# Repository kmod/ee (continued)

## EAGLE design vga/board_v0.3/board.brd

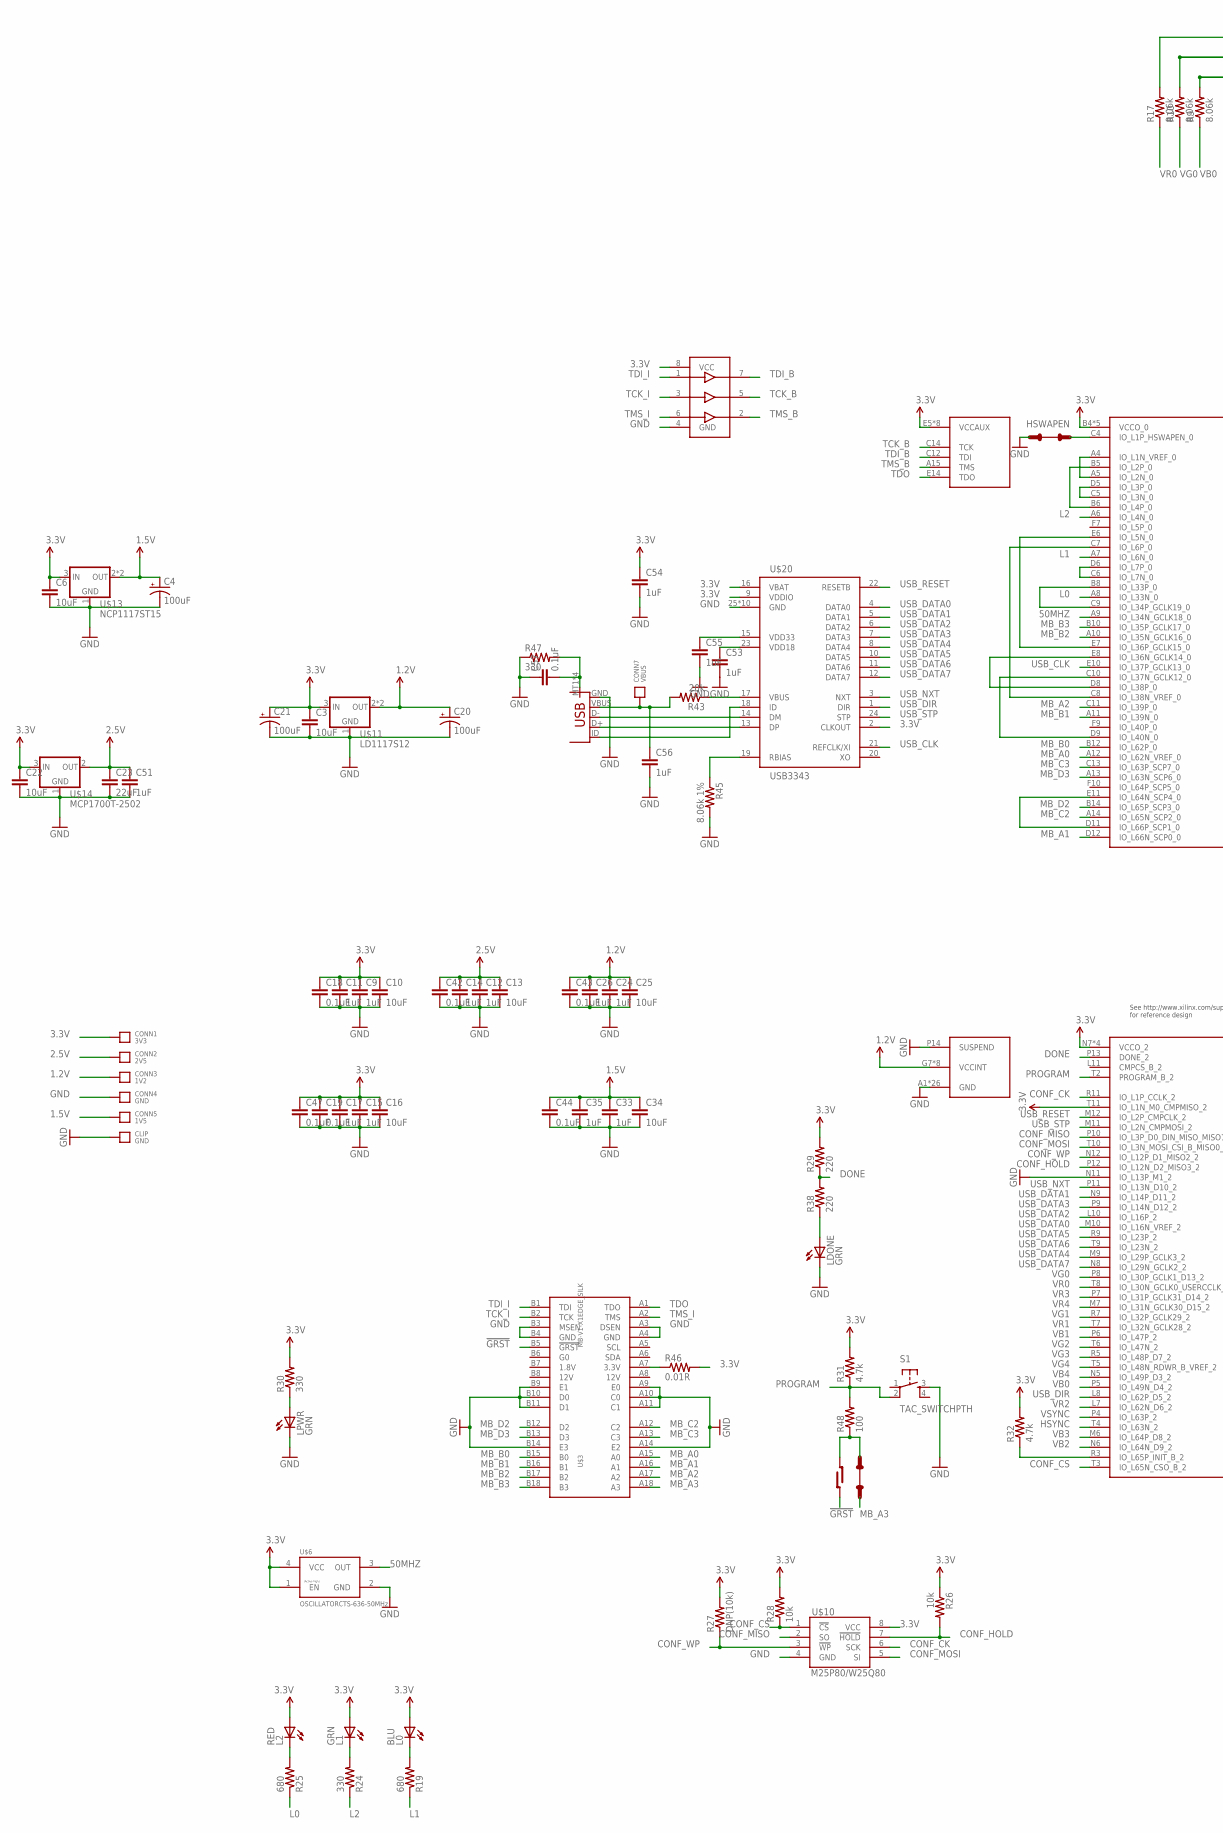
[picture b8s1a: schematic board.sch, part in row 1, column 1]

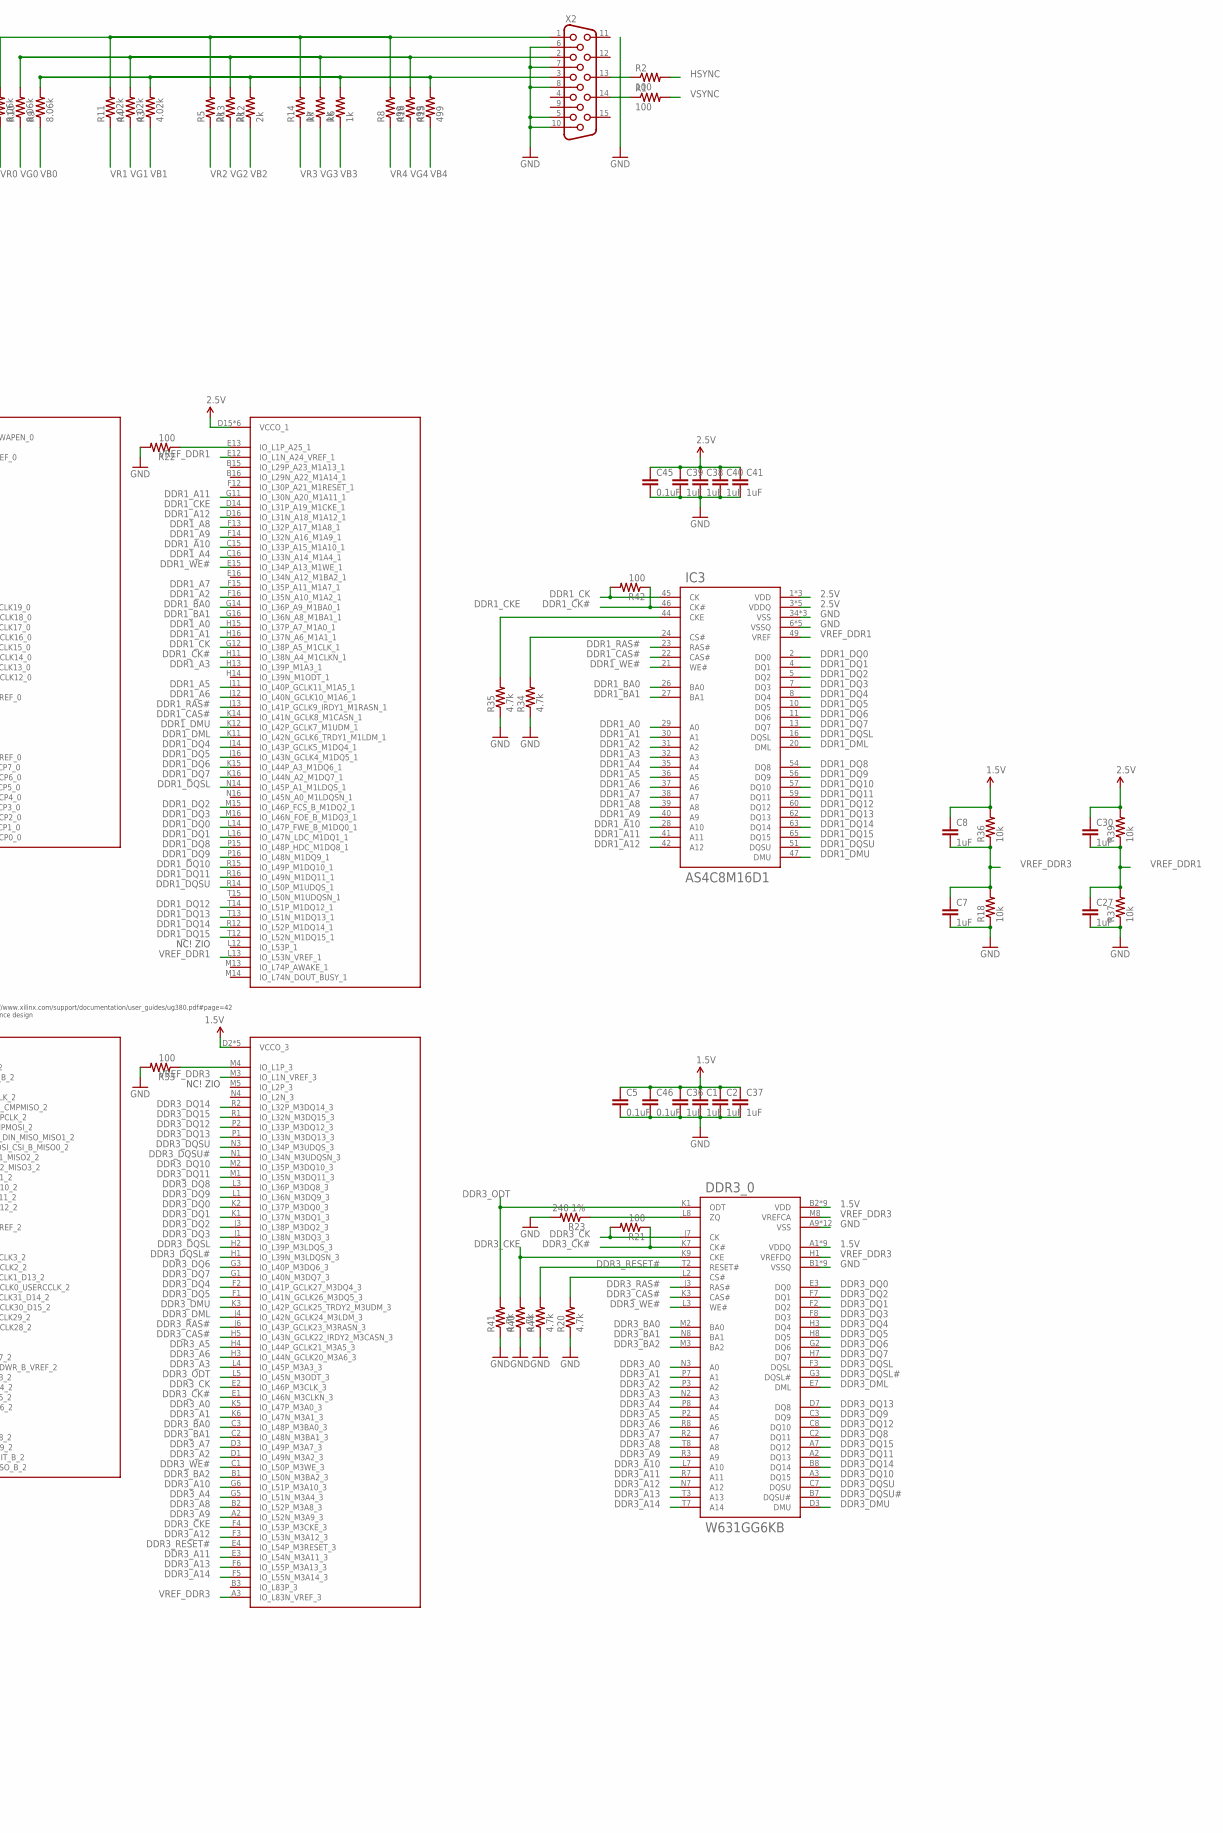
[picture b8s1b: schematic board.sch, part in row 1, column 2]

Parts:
C1, C2, C7, C8, C9, C11, C12, C14, C15, C17, C24, C26, C27, C30, C33, C35, C36, C37, C38, C39, C40, C41, C51, C53, C54, C55, C56: 1uF; 0402-CAP
C3, C6, C10, C13, C16, C22, C25, C34: 10uF; 0603-CAP
C4, C20, C21: 100uF; CAP-5-2
C5, C18, C19, C42, C43, C44, C45, C46, C47: 0.1uF; C0201
C23: 22uF; 0805
C57: 0.1uF; 0402-CAP
CLIP: GND; CLIP-AREA
CONN1: 3V3; HOLE_22AWG
CONN2: 2V5; HOLE_22AWG
CONN3: 1V2; HOLE_22AWG
CONN4: GND; HOLE_22AWG
CONN5: 1V5; HOLE_22AWG
CONN7: VBUS; HOLE_22AWG
DDR3_0: W631GG6KB; BGA96
IC1: XC6S{9,16,25}LX-FT256; XILINX_FT256
IC2: 74LVC3G34; TSSOP8
IC3: AS4C8M16D1; TSOP66-400
JP1: USBMICRO; USB-MICRO
L0: BLU; 0603_LED
L1: GRN; 0603_LED
L2: RED; 0603_LED
LDONE: GRN; 0603_LED
LPWR: GRN; 0603_LED
R1, R2, R21, R22, R33, R48: 100; 0603-RES
R3, R4, R11: 4.02k; 0603-RES
R5, R12, R13: 2k; 0603-RES
R6, R7, R14: 1k; 0603-RES
R8, R15, R16: 499; 0603-RES
R9, R10, R17: 8.06k; 0603-RES
R18, R28, R36, R37, R39: 10k; 0603-RES
R19, R25: 680; 0603-RES
R20, R34, R35, R40, R41, R44: 4.7k; 0402-RES
R23: 240 1%; 0402-RES
R24, R30, R47: 330; 0603-RES
R26: 10k; 0402-RES
R27: DNP(10k); 0402-RES
R29, R38: 220; 0603-RES
R31, R32: 4.7k; 0603-RES
R42: 100; 0402-RES
R43: 20k; 0402-RES
R45: 8.06k 1%; 0603-RES
R46: 0.01R; 0603-RES
S1: TAC_SWITCHPTH; TACTILE-PTH
SB1: SOLDER-BRIDGEOPEN; SOLDER-BRIDGE-OPEN
SB2, SB5: TRACE-CUT
U$3: MB-V1-X1EDGE_SILK; MB-V1-X1-EDGE
U$6: OSCILLATORCTS-636-50MHz; CTS-636
U$10: M25P80/W25Q80; SO08
U$11: LD1117S12; SOT223
U$13: NCP1117ST15; SOT223
U$14: MCP1700T-2502; SOT23-3
U$20: USB3343; QFN24
X2: HDF15H

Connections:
1.2V: C20.1 (+), C24.1, C25.1, C26.1, C43.1, CONN3.P, IC1.G7 (VCCINT), IC1.G9 (VCCINT), IC1.H8 (VCCINT), IC1.H10 (VCCINT), IC1.J7 (VCCINT), IC1.J9 (VCCINT), IC1.K8 (VCCINT), IC1.K10 (VCCINT), U$11.2 (OUT), U$11.4 (OUT)
1.5V: C1.1, C2.1, C4.1 (+), C5.1, C8.1, C33.1, C34.1, C35.1, C36.1, C37.1, C44.1, C46.1, CONN5.P, DDR3_0.A1 (VDDQ), DDR3_0.A8 (VDDQ), DDR3_0.B2 (VDD), DDR3_0.C1 (VDDQ), DDR3_0.C9 (VDDQ), DDR3_0.D2 (VDDQ), DDR3_0.D9 (VDD), DDR3_0.E9 (VDDQ), DDR3_0.F1 (VDDQ), DDR3_0.G7 (VDD), DDR3_0.H2 (VDDQ), DDR3_0.H9 (VDDQ), DDR3_0.K2 (VDD), DDR3_0.K8 (VDD), DDR3_0.N1 (VDD), DDR3_0.N9 (VDD), DDR3_0.R1 (VDD), DDR3_0.R9 (VDD), IC1.D2 (VCCO_3), IC1.G4 (VCCO_3), IC1.J2 (VCCO_3), IC1.K4 (VCCO_3), IC1.N2 (VCCO_3), R36.2, U$13.2 (OUT), U$13.4 (OUT)
2.5V: C12.1, C13.1, C14.1, C23.1, C30.1, C38.1, C39.1, C40.1, C41.1, C42.1, C45.1, C51.1, CONN2.P, IC1.D15 (VCCO_1), IC1.G13 (VCCO_1), IC1.J15 (VCCO_1), IC1.K13 (VCCO_1), IC1.N15 (VCCO_1), IC1.R13 (VCCO_1), IC3.1 (VDD), IC3.3 (VDDQ), IC3.9 (VDDQ), IC3.15 (VDDQ), IC3.18 (VDD), IC3.33 (VDD), IC3.55 (VDDQ), IC3.61 (VDDQ), R39.2, U$14.2 (OUT)
3.3V: C3.1, C6.1, C9.1, C10.1, C11.1, C15.1, C16.1, C17.1, C18.1, C19.1, C21.1 (+), C22.1, C47.1, C54.1, CONN1.P, IC1.B4 (VCCO_0), IC1.B9 (VCCO_0), IC1.B13 (VCCO_0), IC1.D7 (VCCO_0), IC1.D10 (VCCO_0), IC1.E5 (VCCAUX), IC1.F8 (VCCAUX), IC1.F11 (VCCAUX), IC1.G10 (VCCAUX), IC1.H6 (VCCAUX), IC1.J10 (VCCAUX), IC1.L6 (VCCAUX), IC1.L9 (VCCAUX), IC1.N7 (VCCO_2), IC1.N10 (VCCO_2), IC1.R4 (VCCO_2), IC1.R8 (VCCO_2), IC1.T11 (IO_L1N_M0_CMPMISO_2), IC2.8 (VCC), L0.A, L1.A, L2.A, R26.1, R27.2, R28.2, R29.2, R30.2, R31.2, R32.2, R46.2, U$6.1 (EN), U$6.4 (VCC), U$10.8 (VCC), U$11.3 (IN), U$13.3 (IN), U$14.3 (IN), U$20.2 (CLKOUT), U$20.9 (VDDIO), U$20.16 (VBAT)
50MHZ: IC1.A9 (IO_L34N_GCLK18_0), U$6.3 (OUT)
!GRST: SB1.L1, SB1.L2, U$3.B5 (!GRST)
CONF_CK: IC1.R11 (IO_L1P_CCLK_2), U$10.6 (SCK)
CONF_CS: IC1.T3 (IO_L65N_CSO_B_2), R28.1, U$10.1 (!CS)
CONF_HOLD: IC1.P12 (IO_L12N_D2_MISO3_2), R26.2, U$10.7 (!HOLD)
CONF_MISO: IC1.P10 (IO_L3P_D0_DIN_MISO_MISO1_2), U$10.2 (SO)
CONF_MOSI: IC1.T10 (IO_L3N_MOSI_CSI_B_MISO0_2), U$10.5 (SI)
CONF_WP: IC1.N12 (IO_L12P_D1_MISO2_2), R27.1, U$10.3 (!WP)
DDR1_A0: IC1.H15 (IO_L37P_A7_M1A0_1), IC3.29 (A0)
DDR1_A1: IC1.H16 (IO_L37N_A6_M1A1_1), IC3.30 (A1)
DDR1_A2: IC1.F16 (IO_L35N_A10_M1A2_1), IC3.31 (A2)
DDR1_A3: IC1.H13 (IO_L39P_M1A3_1), IC3.32 (A3)
DDR1_A4: IC1.C16 (IO_L33N_A14_M1A4_1), IC3.35 (A4)
DDR1_A5: IC1.J11 (IO_L40P_GCLK11_M1A5_1), IC3.36 (A5)
DDR1_A6: IC1.J12 (IO_L40N_GCLK10_M1A6_1), IC3.37 (A6)
DDR1_A7: IC1.F15 (IO_L35P_A11_M1A7_1), IC3.38 (A7)
DDR1_A8: IC1.F13 (IO_L32P_A17_M1A8_1), IC3.39 (A8)
DDR1_A9: IC1.F14 (IO_L32N_A16_M1A9_1), IC3.40 (A9)
DDR1_A10: IC1.C15 (IO_L33P_A15_M1A10_1), IC3.28 (A10)
DDR1_A11: IC1.G11 (IO_L30N_A20_M1A11_1), IC3.41 (A11)
DDR1_A12: IC1.D16 (IO_L31N_A18_M1A12_1), IC3.42 (A12)
DDR1_BA0: IC1.G14 (IO_L36P_A9_M1BA0_1), IC3.26 (BA0)
DDR1_BA1: IC1.G16 (IO_L36N_A8_M1BA1_1), IC3.27 (BA1)
DDR1_CAS#: IC1.K14 (IO_L41N_GCLK8_M1CASN_1), IC3.22 (CAS#)
DDR1_CK: IC1.G12 (IO_L38P_A5_M1CLK_1), IC3.45 (CK), R42.2
DDR1_CK#: IC1.H11 (IO_L38N_A4_M1CLKN_1), IC3.46 (CK#), R42.1
DDR1_CKE: IC1.D14 (IO_L31P_A19_M1CKE_1), IC3.44 (CKE), R35.2
DDR1_CS#: IC3.24 (CS#), R34.2
DDR1_DML: IC1.K11 (IO_L42N_GCLK6_TRDY1_M1LDM_1), IC3.20 (DML)
DDR1_DMU: IC1.K12 (IO_L42P_GCLK7_M1UDM_1), IC3.47 (DMU)
DDR1_DQ0: IC1.L14 (IO_L47P_FWE_B_M1DQ0_1), IC3.2 (DQ0)
DDR1_DQ1: IC1.L16 (IO_L47N_LDC_M1DQ1_1), IC3.4 (DQ1)
DDR1_DQ2: IC1.M15 (IO_L46P_FCS_B_M1DQ2_1), IC3.5 (DQ2)
DDR1_DQ3: IC1.M16 (IO_L46N_FOE_B_M1DQ3_1), IC3.7 (DQ3)
DDR1_DQ4: IC1.J14 (IO_L43P_GCLK5_M1DQ4_1), IC3.8 (DQ4)
DDR1_DQ5: IC1.J16 (IO_L43N_GCLK4_M1DQ5_1), IC3.10 (DQ5)
DDR1_DQ6: IC1.K15 (IO_L44P_A3_M1DQ6_1), IC3.11 (DQ6)
DDR1_DQ7: IC1.K16 (IO_L44N_A2_M1DQ7_1), IC3.13 (DQ7)
DDR1_DQ8: IC1.P15 (IO_L48P_HDC_M1DQ8_1), IC3.54 (DQ8)
DDR1_DQ9: IC1.P16 (IO_L48N_M1DQ9_1), IC3.56 (DQ9)
DDR1_DQ10: IC1.R15 (IO_L49P_M1DQ10_1), IC3.57 (DQ10)
DDR1_DQ11: IC1.R16 (IO_L49N_M1DQ11_1), IC3.59 (DQ11)
DDR1_DQ12: IC1.T14 (IO_L51P_M1DQ12_1), IC3.60 (DQ12)
DDR1_DQ13: IC1.T13 (IO_L51N_M1DQ13_1), IC3.62 (DQ13)
DDR1_DQ14: IC1.R12 (IO_L52P_M1DQ14_1), IC3.63 (DQ14)
DDR1_DQ15: IC1.T12 (IO_L52N_M1DQ15_1), IC3.65 (DQ15)
DDR1_DQSL: IC1.N14 (IO_L45P_A1_M1LDQS_1), IC3.16 (DQSL)
DDR1_DQSU: IC1.R14 (IO_L50P_M1UDQS_1), IC3.51 (DQSU)
DDR1_RAS#: IC1.J13 (IO_L41P_GCLK9_IRDY1_M1RASN_1), IC3.23 (RAS#)
DDR1_WE#: IC1.E15 (IO_L34P_A13_M1WE_1), IC3.21 (WE#)
DDR3_A0: DDR3_0.N3 (A0), IC1.K5 (IO_L47P_M3A0_3)
DDR3_A1: DDR3_0.P7 (A1), IC1.K6 (IO_L47N_M3A1_3)
DDR3_A2: DDR3_0.P3 (A2), IC1.D1 (IO_L49N_M3A2_3)
DDR3_A3: DDR3_0.N2 (A3), IC1.L4 (IO_L45P_M3A3_3)
DDR3_A4: DDR3_0.P8 (A4), IC1.G5 (IO_L51N_M3A4_3)
DDR3_A5: DDR3_0.P2 (A5), IC1.H4 (IO_L44P_GCLK21_M3A5_3)
DDR3_A6: DDR3_0.R8 (A6), IC1.H3 (IO_L44N_GCLK20_M3A6_3)
DDR3_A7: DDR3_0.R2 (A7), IC1.D3 (IO_L49P_M3A7_3)
DDR3_A8: DDR3_0.T8 (A8), IC1.B2 (IO_L52P_M3A8_3)
DDR3_A9: DDR3_0.R3 (A9), IC1.A2 (IO_L52N_M3A9_3)
DDR3_A10: DDR3_0.L7 (A10), IC1.G6 (IO_L51P_M3A10_3)
DDR3_A11: DDR3_0.R7 (A11), IC1.E3 (IO_L54N_M3A11_3)
DDR3_A12: DDR3_0.N7 (A12), IC1.F3 (IO_L53N_M3A12_3)
DDR3_A13: DDR3_0.T3 (A13), IC1.F6 (IO_L55P_M3A13_3)
DDR3_A14: DDR3_0.T7 (A14), IC1.F5 (IO_L55N_M3A14_3)
DDR3_BA0: DDR3_0.M2 (BA0), IC1.C3 (IO_L48P_M3BA0_3)
DDR3_BA1: DDR3_0.N8 (BA1), IC1.C2 (IO_L48N_M3BA1_3)
DDR3_BA2: DDR3_0.M3 (BA2), IC1.B1 (IO_L50N_M3BA2_3)
DDR3_CAS#: DDR3_0.K3 (CAS#), IC1.H5 (IO_L43N_GCLK22_IRDY2_M3CASN_3)
DDR3_CK: DDR3_0.J7 (CK), IC1.E2 (IO_L46P_M3CLK_3), R21.2
DDR3_CK#: DDR3_0.K7 (CK#), IC1.E1 (IO_L46N_M3CLKN_3), R21.1
DDR3_CKE: DDR3_0.K9 (CKE), IC1.F4 (IO_L53P_M3CKE_3), R40.2
DDR3_CS#: DDR3_0.L2 (CS#), R20.2
DDR3_DML: DDR3_0.E7 (DML), IC1.J4 (IO_L42N_GCLK24_M3LDM_3)
DDR3_DMU: DDR3_0.D3 (DMU), IC1.K3 (IO_L42P_GCLK25_TRDY2_M3UDM_3)
DDR3_DQ0: DDR3_0.E3 (DQ0), IC1.K2 (IO_L37P_M3DQ0_3)
DDR3_DQ1: DDR3_0.F2 (DQ2), IC1.K1 (IO_L37N_M3DQ1_3)
DDR3_DQ2: DDR3_0.F7 (DQ1), IC1.J3 (IO_L38P_M3DQ2_3)
DDR3_DQ3: DDR3_0.F8 (DQ3), IC1.J1 (IO_L38N_M3DQ3_3)
DDR3_DQ4: DDR3_0.H3 (DQ4), IC1.F2 (IO_L41P_GCLK27_M3DQ4_3)
DDR3_DQ5: DDR3_0.H8 (DQ5), IC1.F1 (IO_L41N_GCLK26_M3DQ5_3)
DDR3_DQ6: DDR3_0.G2 (DQ6), IC1.G3 (IO_L40P_M3DQ6_3)
DDR3_DQ7: DDR3_0.H7 (DQ7), IC1.G1 (IO_L40N_M3DQ7_3)
DDR3_DQ8: DDR3_0.C2 (DQ11), IC1.L3 (IO_L36P_M3DQ8_3)
DDR3_DQ9: DDR3_0.C3 (DQ9), IC1.L1 (IO_L36N_M3DQ9_3)
DDR3_DQ10: DDR3_0.A3 (DQ15), IC1.M2 (IO_L35P_M3DQ10_3)
DDR3_DQ11: DDR3_0.A2 (DQ13), IC1.M1 (IO_L35N_M3DQ11_3)
DDR3_DQ12: DDR3_0.C8 (DQ10), IC1.P2 (IO_L33P_M3DQ12_3)
DDR3_DQ13: DDR3_0.D7 (DQ8), IC1.P1 (IO_L33N_M3DQ13_3)
DDR3_DQ14: DDR3_0.B8 (DQ14), IC1.R2 (IO_L32P_M3DQ14_3)
DDR3_DQ15: DDR3_0.A7 (DQ12), IC1.R1 (IO_L32N_M3DQ15_3)
DDR3_DQSL: DDR3_0.F3 (DQSL), IC1.H2 (IO_L39P_M3LDQS_3)
DDR3_DQSL#: DDR3_0.G3 (DQSL#), IC1.H1 (IO_L39N_M3LDQSN_3)
DDR3_DQSU: DDR3_0.C7 (DQSU), IC1.N3 (IO_L34P_M3UDQS_3)
DDR3_DQSU#: DDR3_0.B7 (DQSU#), IC1.N1 (IO_L34N_M3UDQSN_3)
DDR3_ODT: DDR3_0.K1 (ODT), IC1.L5 (IO_L45N_M3ODT_3), R41.2
DDR3_RAS#: DDR3_0.J3 (RAS#), IC1.J6 (IO_L43P_GCLK23_M3RASN_3)
DDR3_RESET#: DDR3_0.T2 (RESET#), IC1.E4 (IO_L54P_M3RESET_3), R44.2
DDR3_WE#: DDR3_0.L3 (WE#), IC1.C1 (IO_L50P_M3WE_3)
DDR3_ZQ: DDR3_0.L8 (ZQ), R23.1
DONE: IC1.P13 (DONE_2), R29.1, R38.2
GND: C1.2, C2.2, C3.2, C4.2 (-), C5.2, C6.2, C7.2, C9.2, C10.2, C11.2, C12.2, C13.2, C14.2, C15.2, C16.2, C17.2, C18.2, C19.2, C20.2 (-), C21.2 (-), C22.2, C23.2, C24.2, C25.2, C26.2, C27.2, C33.2, C34.2, C35.2, C36.2, C37.2, C38.2, C39.2, C40.2, C41.2, C42.2, C43.2, C44.2, C45.2, C46.2, C47.2, C51.2, C53.2, C54.2, C55.2, C56.2, C57.1, CLIP.P$1, CLIP.P$2, CONN4.P, DDR3_0.A9 (VSS), DDR3_0.B1 (VSSQ), DDR3_0.B3 (VSS), DDR3_0.B9 (VSSQ), DDR3_0.D1 (VSSQ), DDR3_0.D8 (VSSQ), DDR3_0.E1 (VSS), DDR3_0.E2 (VSSQ), DDR3_0.E8 (VSSQ), DDR3_0.F9 (VSSQ), DDR3_0.G1 (VSSQ), DDR3_0.G8 (VSS), DDR3_0.G9 (VSSQ), DDR3_0.J2 (VSS), DDR3_0.J8 (VSS), DDR3_0.M1 (VSS), DDR3_0.M9 (VSS), DDR3_0.P1 (VSS), DDR3_0.P9 (VSS), DDR3_0.T1 (VSS), DDR3_0.T9 (VSS), IC1.A1 (GND), IC1.A16 (GND), IC1.B7 (GND), IC1.B11 (GND), IC1.D4 (GND), IC1.D13 (GND), IC1.E9 (GND), IC1.G2 (GND), IC1.G8 (GND), IC1.G15 (GND), IC1.H7 (GND), IC1.H9 (GND), IC1.H12 (GND), IC1.J5 (GND), IC1.J8 (GND), IC1.K7 (GND), IC1.K9 (GND), IC1.L2 (GND), IC1.L15 (GND), IC1.M8 (GND), IC1.N11 (IO_L13P_M1_2), IC1.N13 (GND), IC1.P3 (GND), IC1.P14 (SUSPEND), IC1.R6 (GND), IC1.R10 (GND), IC1.T1 (GND), IC1.T16 (GND), IC2.4 (GND), IC3.6 (VSSQ), IC3.12 (VSSQ), IC3.34 (VSS), IC3.48 (VSS), IC3.52 (VSSQ), IC3.58 (VSSQ), IC3.64 (VSSQ), IC3.66 (VSS), JP1.GND, LDONE.C, LPWR.C, R18.1, R20.1, R22.2, R23.2, R33.2, R34.1, R35.1, R37.1, R40.1, R41.1, R44.1, R45.2, R47.1, S1.3, SB5.R1, U$3.A3 (DSEN), U$3.A4 (GND), U$3.A9 (E0), U$3.A10 (C0), U$3.A11 (C1), U$3.A14 (E2), U$3.B3 (MSEN), U$3.B4 (GND), U$3.B9 (E1), U$3.B10 (D0), U$3.B11 (D1), U$3.B14 (E3), U$6.2 (GND), U$10.4 (GND), U$11.1 (GND), U$13.1 (GND), U$14.1 (GND), U$20.25 (GND), U$20.26 (GND), U$20.27 (GND), U$20.28 (GND), U$20.29 (GND), U$20.30 (GND), U$20.31 (GND), U$20.32 (GND), U$20.33 (GND), U$20.34 (GND), X2.5, X2.6, X2.7, X2.8, X2.10
HSWAPEN: IC1.C4 (IO_L1P_HSWAPEN_0), SB5.L1
HSYNC: IC1.T4 (IO_L63N_2), R2.2
INIT_B: IC1.R3 (IO_L65P_INIT_B_2), R32.1
L0: IC1.A8 (IO_L33N_0), R25.1
L1: IC1.A7 (IO_L6N_0), R19.1
L2: IC1.A6 (IO_L4N_0), R24.1
MB_A0: IC1.A12 (IO_L62N_VREF_0), U$3.A15 (A0)
MB_A1: IC1.D12 (IO_L66N_SCP0_0), U$3.A16 (A1)
MB_A2: IC1.C11 (IO_L39P_0), U$3.A17 (A2)
MB_A3: SB2.L1, U$3.A18 (A3)
MB_B0: IC1.B12 (IO_L62P_0), U$3.B15 (B0)
MB_B1: IC1.A11 (IO_L39N_0), U$3.B16 (B1)
MB_B2: IC1.A10 (IO_L35N_GCLK16_0), U$3.B17 (B2)
MB_B3: IC1.B10 (IO_L35P_GCLK17_0), U$3.B18 (B3)
MB_C2: IC1.A14 (IO_L65N_SCP2_0), U$3.A12 (C2)
MB_C3: IC1.C13 (IO_L63P_SCP7_0), U$3.A13 (C3)
MB_D2: IC1.B14 (IO_L65P_SCP3_0), U$3.B12 (D2)
MB_D3: IC1.A13 (IO_L63N_SCP6_0), U$3.B13 (D3)
unnamed: R1.1, X2.14
unnamed: R2.1, X2.13
unnamed: R4.2, R7.2, R10.2, R13.2, R16.2, X2.2
unnamed: R5.2, R8.2, R11.2, R14.2, R17.2, X2.1
unnamed: R46.1, U$3.A7 (3.3V)
unnamed: C56.1, CONN7.P, JP1.VBUS, R43.2
unnamed: L0.C, R19.2
unnamed: L1.C, R24.2
unnamed: L2.C, R25.2
unnamed: R3.2, R6.2, R9.2, R12.2, R15.2, X2.3
unnamed: IC1.E13 (IO_L1P_A25_1), R22.1
unnamed: LPWR.A, R30.1
unnamed: C57.2, JP1.MT1 (SHELL), JP1.MT2 (SHELL), JP1.P$1 (SHELL), JP1.P$2 (SHELL), R47.2
unnamed: LDONE.A, R38.1
unnamed: IC1.A4 (IO_L1N_VREF_0), IC1.A5 (IO_L2N_0)
unnamed: R45.1, U$20.19 (RBIAS)
unnamed: R43.1, U$20.17 (VBUS)
unnamed: IC1.B5 (IO_L2P_0), IC1.B6 (IO_L4P_0)
unnamed: IC1.C5 (IO_L3N_0), IC1.D5 (IO_L3P_0)
unnamed: IC1.C6 (IO_L7N_0), IC1.D6 (IO_L7P_0)
unnamed: IC1.C7 (IO_L6P_0), IC1.C8 (IO_L38N_VREF_0)
unnamed: IC1.B8 (IO_L33P_0), IC1.C9 (IO_L34P_GCLK19_0)
unnamed: IC1.C10 (IO_L37N_GCLK12_0), IC1.D9 (IO_L40N_0)
unnamed: IC1.D8 (IO_L38P_0), IC1.E8 (IO_L36N_GCLK14_0)
unnamed: IC1.M4 (IO_L1P_3), R33.1
unnamed: IC1.E6 (IO_L5N_0), IC1.E7 (IO_L36P_GCLK15_0)
unnamed: IC1.D11 (IO_L66P_SCP1_0), IC1.E11 (IO_L64N_SCP4_0)
unnamed: R48.1, SB1.R1, SB1.R2, SB2.R1
PROGRAM: IC1.T2 (PROGRAM_B_2), R31.1, R48.2, S1.2
TCK_B: IC1.C14 (TCK), IC2.5 (2Y)
TCK_I: IC2.3 (2A), U$3.B2 (TCK)
TDI_B: IC1.C12 (TDI), IC2.7 (1Y)
TDI_I: IC2.1 (1A), U$3.B1 (TDI)
TDO: IC1.E14 (TDO), U$3.A1 (TDO)
TMS_B: IC1.A15 (TMS), IC2.2 (3Y)
TMS_I: IC2.6 (3A), U$3.A2 (TMS)
USB_1.8V: C53.1, U$20.23 (VDD18)
USB_3.3V: C55.1, U$20.15 (VDD33)
USB_CLK: IC1.E10 (IO_L37P_GCLK13_0), U$20.21 (REFCLK/XI)
USB_DATA0: IC1.M10 (IO_L16N_VREF_2), U$20.4 (DATA0)
USB_DATA1: IC1.N9 (IO_L14P_D11_2), U$20.5 (DATA1)
USB_DATA2: IC1.L10 (IO_L16P_2), U$20.6 (DATA2)
USB_DATA3: IC1.P9 (IO_L14N_D12_2), U$20.7 (DATA3)
USB_DATA4: IC1.M9 (IO_L29P_GCLK3_2), U$20.8 (DATA4)
USB_DATA5: IC1.R9 (IO_L23P_2), U$20.10 (DATA5)
USB_DATA6: IC1.T9 (IO_L23N_2), U$20.11 (DATA6)
USB_DATA7: IC1.N8 (IO_L29N_GCLK2_2), U$20.12 (DATA7)
USB_DIR: IC1.L8 (IO_L62P_D5_2), U$20.1 (DIR)
USB_DM: JP1.D-, U$20.14 (DM)
USB_DP: JP1.D+, U$20.13 (DP)
USB_ID: JP1.ID, U$20.18 (ID)
USB_NXT: IC1.P11 (IO_L13N_D10_2), U$20.3 (NXT)
USB_RESET: IC1.M12 (IO_L2P_CMPCLK_2), U$20.22 (RESETB)
USB_STP: IC1.M11 (IO_L2N_CMPMOSI_2), U$20.24 (STP)
VB0: IC1.P5 (IO_L49N_D4_2), R9.1
VB1: IC1.P6 (IO_L47P_2), R3.1
VB2: IC1.N6 (IO_L64N_D9_2), R12.1
VB3: IC1.M6 (IO_L64P_D8_2), R6.1
VB4: IC1.N5 (IO_L49P_D3_2), R15.1
VG0: IC1.P8 (IO_L30P_GCLK1_D13_2), R10.1
VG1: IC1.R7 (IO_L32P_GCLK29_2), R4.1
VG2: IC1.T6 (IO_L47N_2), R13.1
VG3: IC1.R5 (IO_L48P_D7_2), R7.1
VG4: IC1.T5 (IO_L48N_RDWR_B_VREF_2), R16.1
VR0: IC1.T8 (IO_L30N_GCLK0_USERCCLK_2), R17.1
VR1: IC1.T7 (IO_L32N_GCLK28_2), R11.1
VR2: IC1.L7 (IO_L62N_D6_2), R5.1
VR3: IC1.P7 (IO_L31P_GCLK31_D14_2), R14.1
VR4: IC1.M7 (IO_L31N_GCLK30_D15_2), R8.1
VREF_DDR1: C27.1, C30.2, IC1.E12 (IO_L1N_A24_VREF_1), IC1.L13 (IO_L53N_VREF_1), IC3.49 (VREF), R37.2, R39.1
VREF_DDR3: C7.1, C8.2, DDR3_0.H1 (VREFDQ), DDR3_0.M8 (VREFCA), IC1.A3 (IO_L83N_VREF_3), IC1.M3 (IO_L1N_VREF_3), R18.2, R36.1
VSYNC: IC1.P4 (IO_L63P_2), R1.2

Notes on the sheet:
See http://www.xilinx.com/support/documentation/user_guides/ug380.pdf#page=42 for reference design
NC! ZIO

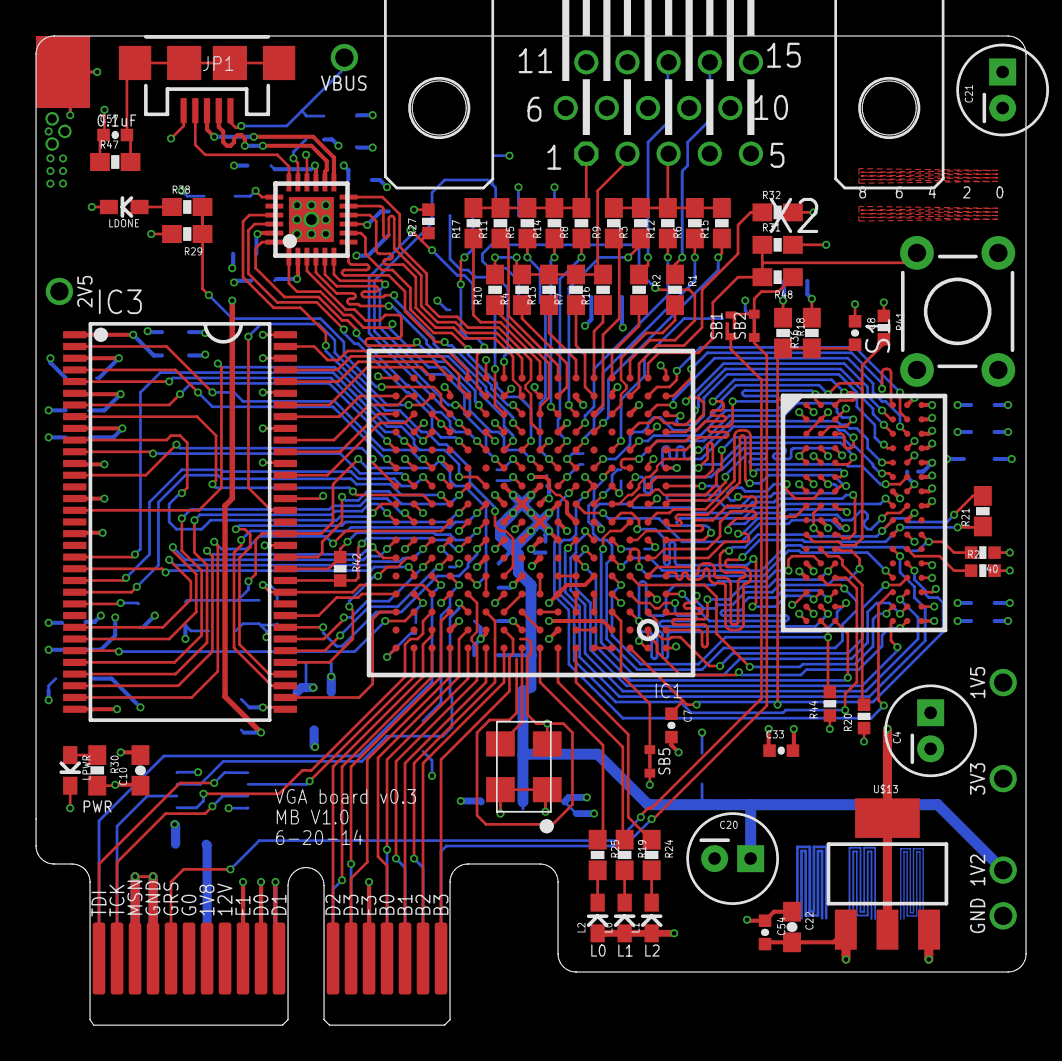
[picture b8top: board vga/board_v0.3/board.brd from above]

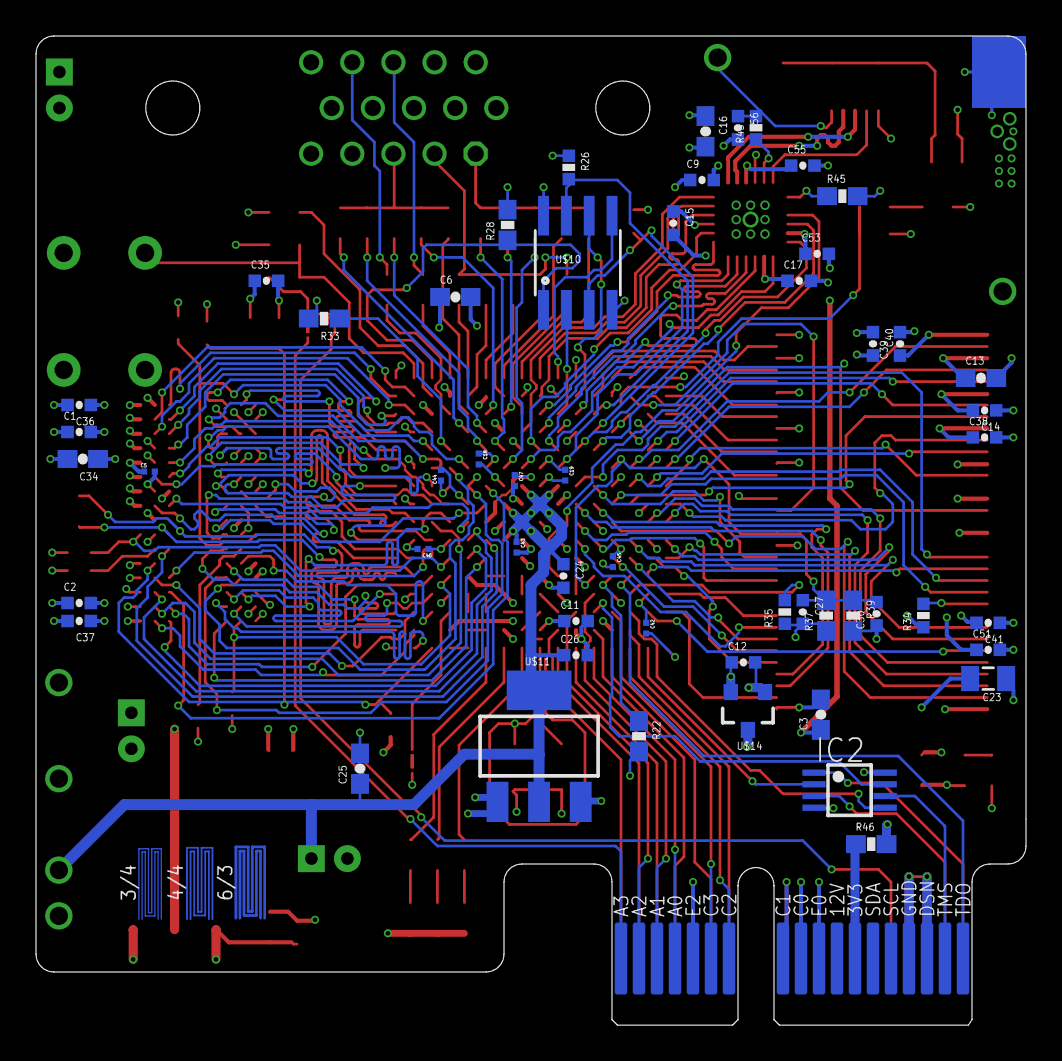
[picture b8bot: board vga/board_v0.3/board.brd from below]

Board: 4 copper layers, 55.0 x 54.9 mm, 126 parts (55 on the bottom side), 196 nets.

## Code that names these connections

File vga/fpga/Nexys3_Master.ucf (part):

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
NET "QuadSpiFlashCS"    LOC="V3"  | IOSTANDARD = "LVCMOS33";  #Bank = MISC, Pin name = IO_L65N_CSO_B_2,                Sch name = CS
#NET "QuadSpiFlashSck"   LOC="R15" | IOSTANDARD = "LVCMOS33";  #Bank = MISC, Pin name = IO_L1P_CCLK_2,                  Sch name = SCK
#NET "QuadSpiFlashDB<0>" LOC="T13" | IOSTANDARD = "LVCMOS33";  #Dual/Quad SPI Flash DB<0>, Bank = MISC, Pin name = IO_L3N_MOSI_CSI_B_MISO0_2, Sch name = SDI

NET "MemAdr<0>"      LOC = "K18" | IOSTANDARD = "LVCMOS33";   #Bank = 1, Pin name = IO_L45N_A0_M1LDQSN,                Sch name = P30-A0
NET "MemAdr<1>"      LOC = "K17" | IOSTANDARD = "LVCMOS33";   #Bank = 1, Pin name = IO_L45P_A1_M1LDQS,                 Sch name = P30-A1
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NET "vgaBlue<1>"     LOC = "R7"  | IOSTANDARD = "LVCMOS33";   # Bank = 2, Pin name = IO_L46P,                          Sch name = BLU1
NET "vgaBlue<2>"     LOC = "T7"  | IOSTANDARD = "LVCMOS33";   # Bank = 2, Pin name = IO_L46N,                          Sch name = BLU2

NET "Hsync"          LOC = "N6"  | IOSTANDARD = "LVCMOS33";   # Bank = 2, Pin name = IO_L47P,                          Sch name = HSYNC
NET "Vsync"          LOC = "P7"  | IOSTANDARD = "LVCMOS33";   # Bank = 2, Pin name = IO_L47N,                          Sch name = VSYNC


## 12 pin connectors
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
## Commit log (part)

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2013-07-28 basic arduino sketch for capacitance measurer circuit
2013-07-28 guess it needs to be called this
2013-07-28 move things around, and add schematic
2013-07-29 output to lcd display as well
2013-08-02 Add v3 of activity_monitor boards; same schematic as v2, but with SMD components and smaller board to fit within 5x5cm
2013-08-10 very simple differential-drive robot
2013-08-10 some misc arduino sketches
2013-08-13 very simple+small arduino-like board
2013-08-24 move all my eagle stuff into this repo
2013-08-24 I'm not sure how this worked before
2013-08-24 don't know why I'm having these mode issues
2013-08-25 simple, non-working bldc driver
2013-08-25 the circuit was broken
2013-08-25 move this
2013-08-30 this works without a prop, how different can that be?
2013-09-03 move some things around
2013-09-03 crossbar-generating script and example
2013-09-04 AM v1.3
2013-09-07 convert bldc driver code to use digital reads with the op-amp based zcd
2013-09-07 switch to directly reading the pins, rather than calling digitalRead
2013-09-07 with the smaller delays, need to turn up the initial #delays
2013-09-09 bldc driver board v0.1
2013-09-14 minor dru updates
2013-09-14 minimega v1.1
2013-09-14 A combined 0.8mm + 0.5mm xQFP breakout board
2013-09-16 SOIC+TSSOP breakout
2013-09-16 minimega v1.1b (qfn, isp header)
2013-09-17 modify this to use the standard SPI pins
2013-09-17 modified ArduinoISO sketch that supports lower programming speeds
2013-09-17 improvements
2013-09-17 move this into the controller
2013-09-18 successfully flipped an output on the CLPD using EXTEST
2013-09-19 increase debugger baud rate from 115.2k to 500k
2013-09-19 homebrew xilinx tools, including svf player
2013-09-19 fix programming configuration to erase the chip first, and improve speed by skipping 'dont care' bits
2013-09-19 better optimization: fetch all bytes, but dont wait after every single pulse
2013-09-19 coolrunner breakout v0.1
2013-09-19 called this 0.1
2013-09-19 simple bga breakout as a process test
2013-09-19 handle more of the logic on the atmega
2013-09-19 optimize the svf reader, down to 7s to program (about 2s startup)
2013-09-19 more optimizations: programming time down to 3 seconds
2013-09-19 cleanup
2013-09-19 last optimization for now; programming time down to 2.5s
2013-09-19 ok, couldnt help myself: improved programming time a little bit more. mostly limited by processing on atmega
2013-09-20 simple arduino makefile
2013-09-20 sick
2013-09-20 damn bga footprints are shown as a bottom view; fix the bga tester. add footprints for smallest xilinx fpga packages
2013-09-22 fpga breakout
2013-09-24 copter control board
2013-09-26 fix some of the names in the bldc eagle files; update driver firmware to work with new board
2013-09-26 note
2013-09-26 starting to organize eagle libraries
2013-09-30 some fixes, filling in values
2013-09-30 testing whether I can route out a 256-BGA on only 2 layers
2013-09-30 add vga project to github repo
2013-09-30 go to 3Mbaud and improve buffering on the computer side
2013-09-30 moving some things around
2013-09-30 trying to get this to work... why is it inferring a 'high' driver??
2013-10-01 update values based on board #1
2013-10-02 got the board somewhat working, though it has trouble driving the new motors
2013-10-02 this seems better
2013-10-03 it seems like the old method is better...
2013-10-03 this seems pretty good, though still shaky at lower powers
2013-10-04 starting to add pci parts
2013-10-04 organizing my eagle library into multiple
2013-10-04 after removing all parts from the monolithic kmod.lbr, restore them but put it in a different place
2013-10-06 modboard in progress
2013-10-15 new bldc driver firmware is speed-controller rather than voltage-controller; not sure if this is better
2013-10-15 eagle updates: moved some parts, added 4-layer osh park dru file
2013-10-15 working on the modboard (backplane, mainboard, arduino)
2013-10-22 finished the base modboards
2013-10-22 vga card done -- first 4-layer board!
2013-12-16 misc changes
2013-12-16 added
2013-12-17 how did this soldermask get screwed up...
2013-12-17 turn off cream (aka paste layer) for pci fingers
2013-12-17 update legend
2013-12-18 can you believe the issues were so simple (needed to drive with stronger current, pin header was faulty!)
2013-12-18 hacky demo but kind of works
2013-12-18 I think counter is right but the electronics are broken
2013-12-19 jtagusaur v0.1
2013-12-19 update vga board with new no-cream pci connector
2013-12-20 fix the mistake in the jtagusaur
2013-12-20 add schematic images and start to write common definitions
2013-12-20 starting to parse the dsl
2013-12-20 kind of got the basic system working, though it has a lot of robustness issues
2013-12-21 update the SparkFun parts repo to the latest version
2013-12-23 I think I got it working somewhat reliably now
2013-12-24 starting to make this more real
2013-12-24 this is starting to come together
2013-12-24 not sure the exact way I want to set this up
2013-12-26 make routing actually work; add another test; need to add a concept of the 'final product' and dont allow reusing connections
2013-12-27 rearrange things a little
2013-12-27 move things around more
2013-12-27 cleaning more up
2013-12-30 crawl the chain
2013-12-30 kind of working now
2013-12-31 emit impact batch file for actual programming
2014-01-02 a lot of this is pretty hacky, but I think it's starting to look good functionality-wise
2014-01-04 test
2014-01-04 test2
2014-01-06 update parts
2014-01-08 small modboard changes
2014-01-10 jtagusaur v0.2
2014-01-10 new version of the testcap with proper alignment so that it will sit flat when connected
2014-01-13 add breadboard breakout
2014-01-16 better
2014-01-16 make led footprint hopefully easier to read
2014-01-22 update some of these values for the leds I decided to populate and their respective brightnesses
2014-01-26 new firmware for the jtagusaur v0.2
2014-01-26 this frickin works!
2014-01-26 the svf file was being created every single time
2014-01-26 add a 'jeds' target to make it easier to build all at once
2014-01-26 add hir/hdr/tir/tdr support to the svf player, which makes it possible to program multiple entities in a chain. use that to test the new boards
2014-02-18 more testing
2014-02-27 clean
2014-03-03 starting to work on stm32 stuff
2014-03-03 common files
2014-03-03 test files
2014-03-03 not sure how I messed that up
2014-03-03 use ldflags
2014-03-03 cooler demo
2014-03-05 working on getting these working
2014-03-06 add the jtag names to these pins as well
2014-03-08 jtagumate: upgraded version of the jtagusaur that uses a 168MHz STM32 instead of a 16MHz ATmega
2014-03-09 oh bleh it was just a problem with the idcode
2014-03-09 debugging why this isn't working; I think it's an eletrical issue
2014-03-10 cool this is all working nicely
2014-03-11 add MB-based BGA test now that that's easy to do
2014-03-11 add a non-bga version so I can make sure it's nothing wrong with the schematic
2014-03-14 re-done version of the vga board, using a spartan-6 tqfp, and following the reference design
2014-03-19 ignore the eagle files I guess
2014-04-02 slightly change the build for this
2014-04-02 got this setup programming my jtagumate
2014-04-02 added dfu programming, some fixes
2014-04-05 some updates to the svf reader (more like svf player)
2014-04-07 minor svf_reader changes, and create a simple EXTEST-based bga tester
2014-04-07 improve enumeration to deal with different IDCODE commands, including commands of different length
2014-04-08 add some initial support for non-router JTAG devices
2014-04-08 simple definitions for fpga project
2014-04-08 try using board-level options to specify where the bitstream should be
2014-04-15 basic 'raytracer' (right now, mandlebrot)
2014-04-15 mandlebrot
2014-04-16 sweet, very basic raycaster
2014-04-19 start working on a new svf_reader, though I think I need to change the approach entirely
2014-04-19 Got a very basic vga thing working, though with some issues -- the blue doesn't seem to be working, and I seem to be missing one of the green bits
2014-04-19 got the vga even more working, though I definitely think one of the pins is messed up
2014-04-20 Use 1280x800 resolution, which seems to be the lowest 16x10 resolution that my Dell 2410 supports
2014-04-20 a new svf_reader, with higher baud rate and no sleeping; can reach 100Kbit
2014-04-21 minor
2014-04-21 another svf_reader version: actually reading the jtag spec and updating+sampling signals at the right times
2014-04-28 ft2232h-based modboard
2014-04-28 Turns out it was working all along? and now the green bit is working too? hw is infuriating
2014-04-28 basic bitbanging
2014-04-28 very simple example that ties it all together!
2014-04-29 I think this mask handling is more correct
2014-05-05 some minor svf_reader debugging improvements... errors are still confounding
2014-05-09 working on CC3000 modboard
2014-05-09 trying to get a bitbang-through-the-fpga spi test working
2014-05-09 sweet, got the SPI working
2014-05-17 ft256 footprint, and spartan-6 schematic for it
2014-05-17 whoops, flip this backside up
2014-06-12 Working on vga board v0.3
2014-06-21 vga board v0.3. added keepout to a bunch of packages
2014-06-28 New components
2014-06-29 work continues on coven boards
2014-06-30 more work on coven
2014-07-09 Initial coven boards: A13 v0.1 card and test socket
2014-07-18 working on more coven boards
2014-07-26 starting to work on programming the new vga board
2014-07-26 move away a bunch of crufty stuff
2014-07-26 Guess I need this
2014-07-26 trying to add old-style endpoint, though I'm not sure it's going to work
2014-07-26 get the legacy reader working within the new framework
2014-07-28 make the old-style jtag programmer work
    I think the fast rate of incoming data was overflowing some buffer
    on the receive side, so manually limit the system to having max
    1050 bytes coming in at once.
2014-07-28 add XVC support to this player
2014-07-28 trying to merge the legacy and new svf readers
    first step: trying to migrate the old svf reader to the new hub class
2014-07-28 trying to merge
2014-07-30 Got the VGA board up and running!
    The resistors had gotten mixed up due to pinswapping,
    so fixed that up in the schematic.
    Copied the code from v0.2, updated the ucf, and it works!
2014-08-01 Added some test coven boards to start narrowing down where the problem is
2014-10-06 minor fix
2014-10-06 misc parts changes I don't remember
2014-10-06 Looks like this was probably the issue: miscopied the linker script
2014-10-06 need to update this
2014-10-06 I think we want -nostdlib?
2014-10-06 Found the problem: bug in the linker script (wrong hardcoded amount of ram)
    I can see why these chips aren't being adopted as much as I would
    have thought based on the techincal merits.
2014-10-06 clean up these definitions a bit
2014-10-06 archive the old version
2014-10-06 rearrange some directories
2014-10-06 urgh some sort of timing issue here
2014-10-13 Make this work with my stm32f405 board
2014-10-13 usb test
2014-11-20 Update the configuration
2014-11-20 Makefile fixes
2014-11-22 Add ISE modifications
2014-11-22 Rename fpga->fpga_memtest, will resurrect the old vga version next
2014-11-22 Resurrect the old vga version
2014-11-23 Ok feel pretty good about this
2014-11-23 Some updates for passing SPI signals through
2014-11-23 Split vga/memtest at the prog layer instead of fpga
2014-11-23 Hmm guess I have to add this too
2014-11-23 more untracked files
2014-11-24 ss was being passed through just hadn't reprogrammed :/
2014-11-24 Refactor the verilog a bit
2014-11-24 read the calib registers
2014-11-26 It works! extremely slow but the ddr1 works
2014-11-26 minor changes to the test script
2014-11-26 Reset everything on ss_n deassertion
2014-12-03 Add lsm330 MB breakout
2014-12-04 A3909 motor driver board
2014-12-15 I'm not sure I believe it, but it looks like the ddr3 section works as well!
2014-12-15 Make the script faster by not waiting for acks
    Still have to wait for read values (don't pipeline data on reads)
    so the limit was ~4x faster (3 writes per read currently).
2014-12-15 Make these more prominent
2015-01-05 Add v0.2 rev of A3909 board
2015-01-05 pwrboard v1.1
2015-05-03 bemicro cv prototyping shield
2016-01-25 Power breakout board
2019-08-04 initial jacket code
